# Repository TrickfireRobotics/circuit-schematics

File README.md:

# circuit-schematics
A repo for storing some of TrickFire's circuit schamtics, diagrams, and other related circuit files

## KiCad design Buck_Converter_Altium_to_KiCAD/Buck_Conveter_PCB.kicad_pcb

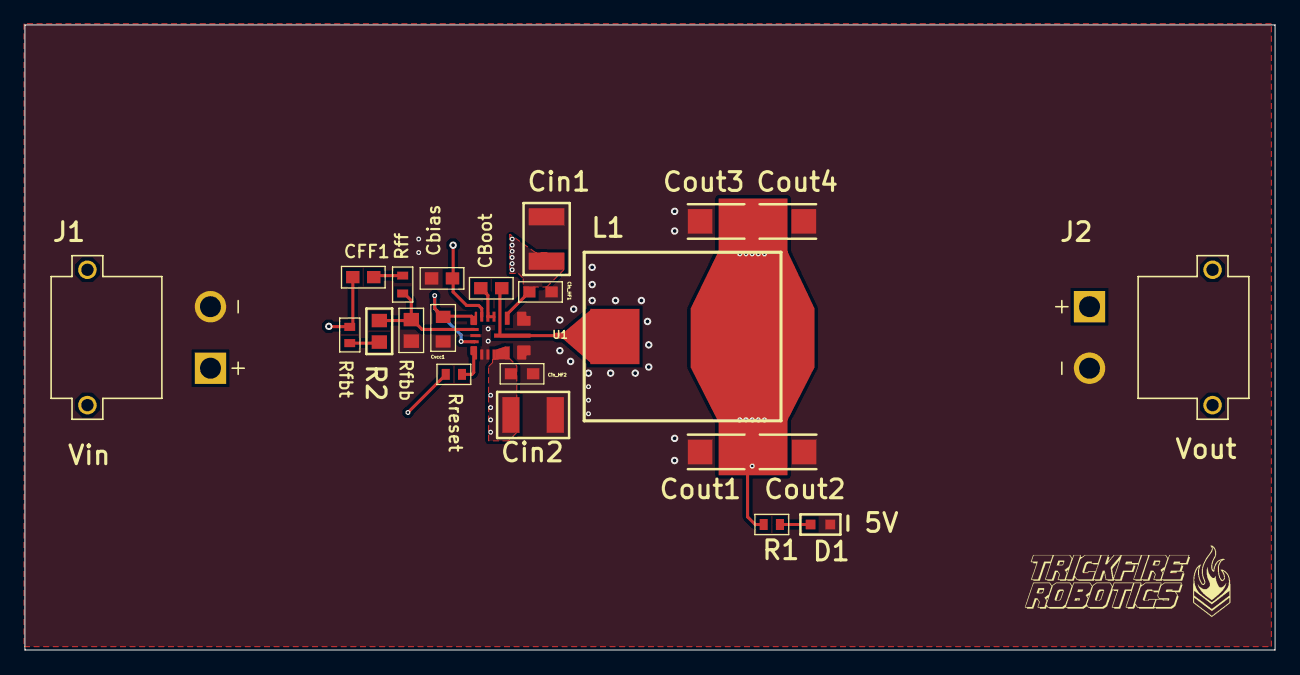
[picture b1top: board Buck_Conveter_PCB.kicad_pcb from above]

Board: 4 copper layers, 101.6 x 50.8 mm, 23 parts (0 on the bottom side), 11 nets.

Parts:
CBoot: 100nF; CBOOT_100NF
CFF1: 5.1pF; CFF_5.1PF
Cbias: 100nF; CBOOT_100NF
Cin1, Cin2: 10uF; CIN_10UF_CAP
Cin_HF1, Cin_HF2: 1uF; 1UF_CINHF
Cout1, Cout2, Cout3, Cout4: 100 uF; 100UF_COUT
Cvcc1: 1uF; CVCC_1UF
D1: LED Indicator; 2V_LED
J1, J2: XT30; XT30PW-M
L1: 3.3uH; 3.3UH INDUCTOR
R1: 100K; 100K RESISTOR
R2: 50; 50_RESISTOR
Rfbb: 24.9K; R_FBB_24.9K
Rfbt: 100K; 100K RESISTOR
Rff: 4.99K; 4.99K_RESISTOR
Rreset: 100K; 100K RESISTOR
U1: LM61495RPHR; LM61495RPHR_IC

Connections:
5V_OUT: CFF1.2, Cbias.2, Cout1.2, Cout2.2, Cout3.2, Cout4.2, J2.1, L1.2, R1.2, Rfbt.2, Rreset.2, U1.5
12V_IN: Cin1.2, Cin2.2, Cin_HF1.2, Cin_HF2.2, J1.1, U1.2, U1.13, U1.14
FB_IN: R2.2, Rfbb.2, Rff.1, U1.7
GND: Cbias.1, Cin1.1, Cin2.1, Cin_HF1.1, Cin_HF2.1, Cout1.1, Cout2.1, Cout3.1, Cout4.1, Cvcc1.1, D1.2, J1.2, J2.2, Rfbb.1, U1.1, U1.8, U1.11, U1.12, U1.15
NetCFF1_1: CFF1.1, Rff.2
NetCboot1_1: CBoot.1, U1.3, U1.4
NetCboot1_2: CBoot.2, L1.1, U1.16
NetD1_1: D1.1, R1.1
NetR2_1: R2.1, Rfbt.1
NetRreset_1: Rreset.1, U1.10
VCC: Cvcc1.2, U1.6, U1.9

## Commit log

2024-06-04 kicad conversion files
2024-06-07 Updated pcb with LED
2024-06-23 Updated PCB
